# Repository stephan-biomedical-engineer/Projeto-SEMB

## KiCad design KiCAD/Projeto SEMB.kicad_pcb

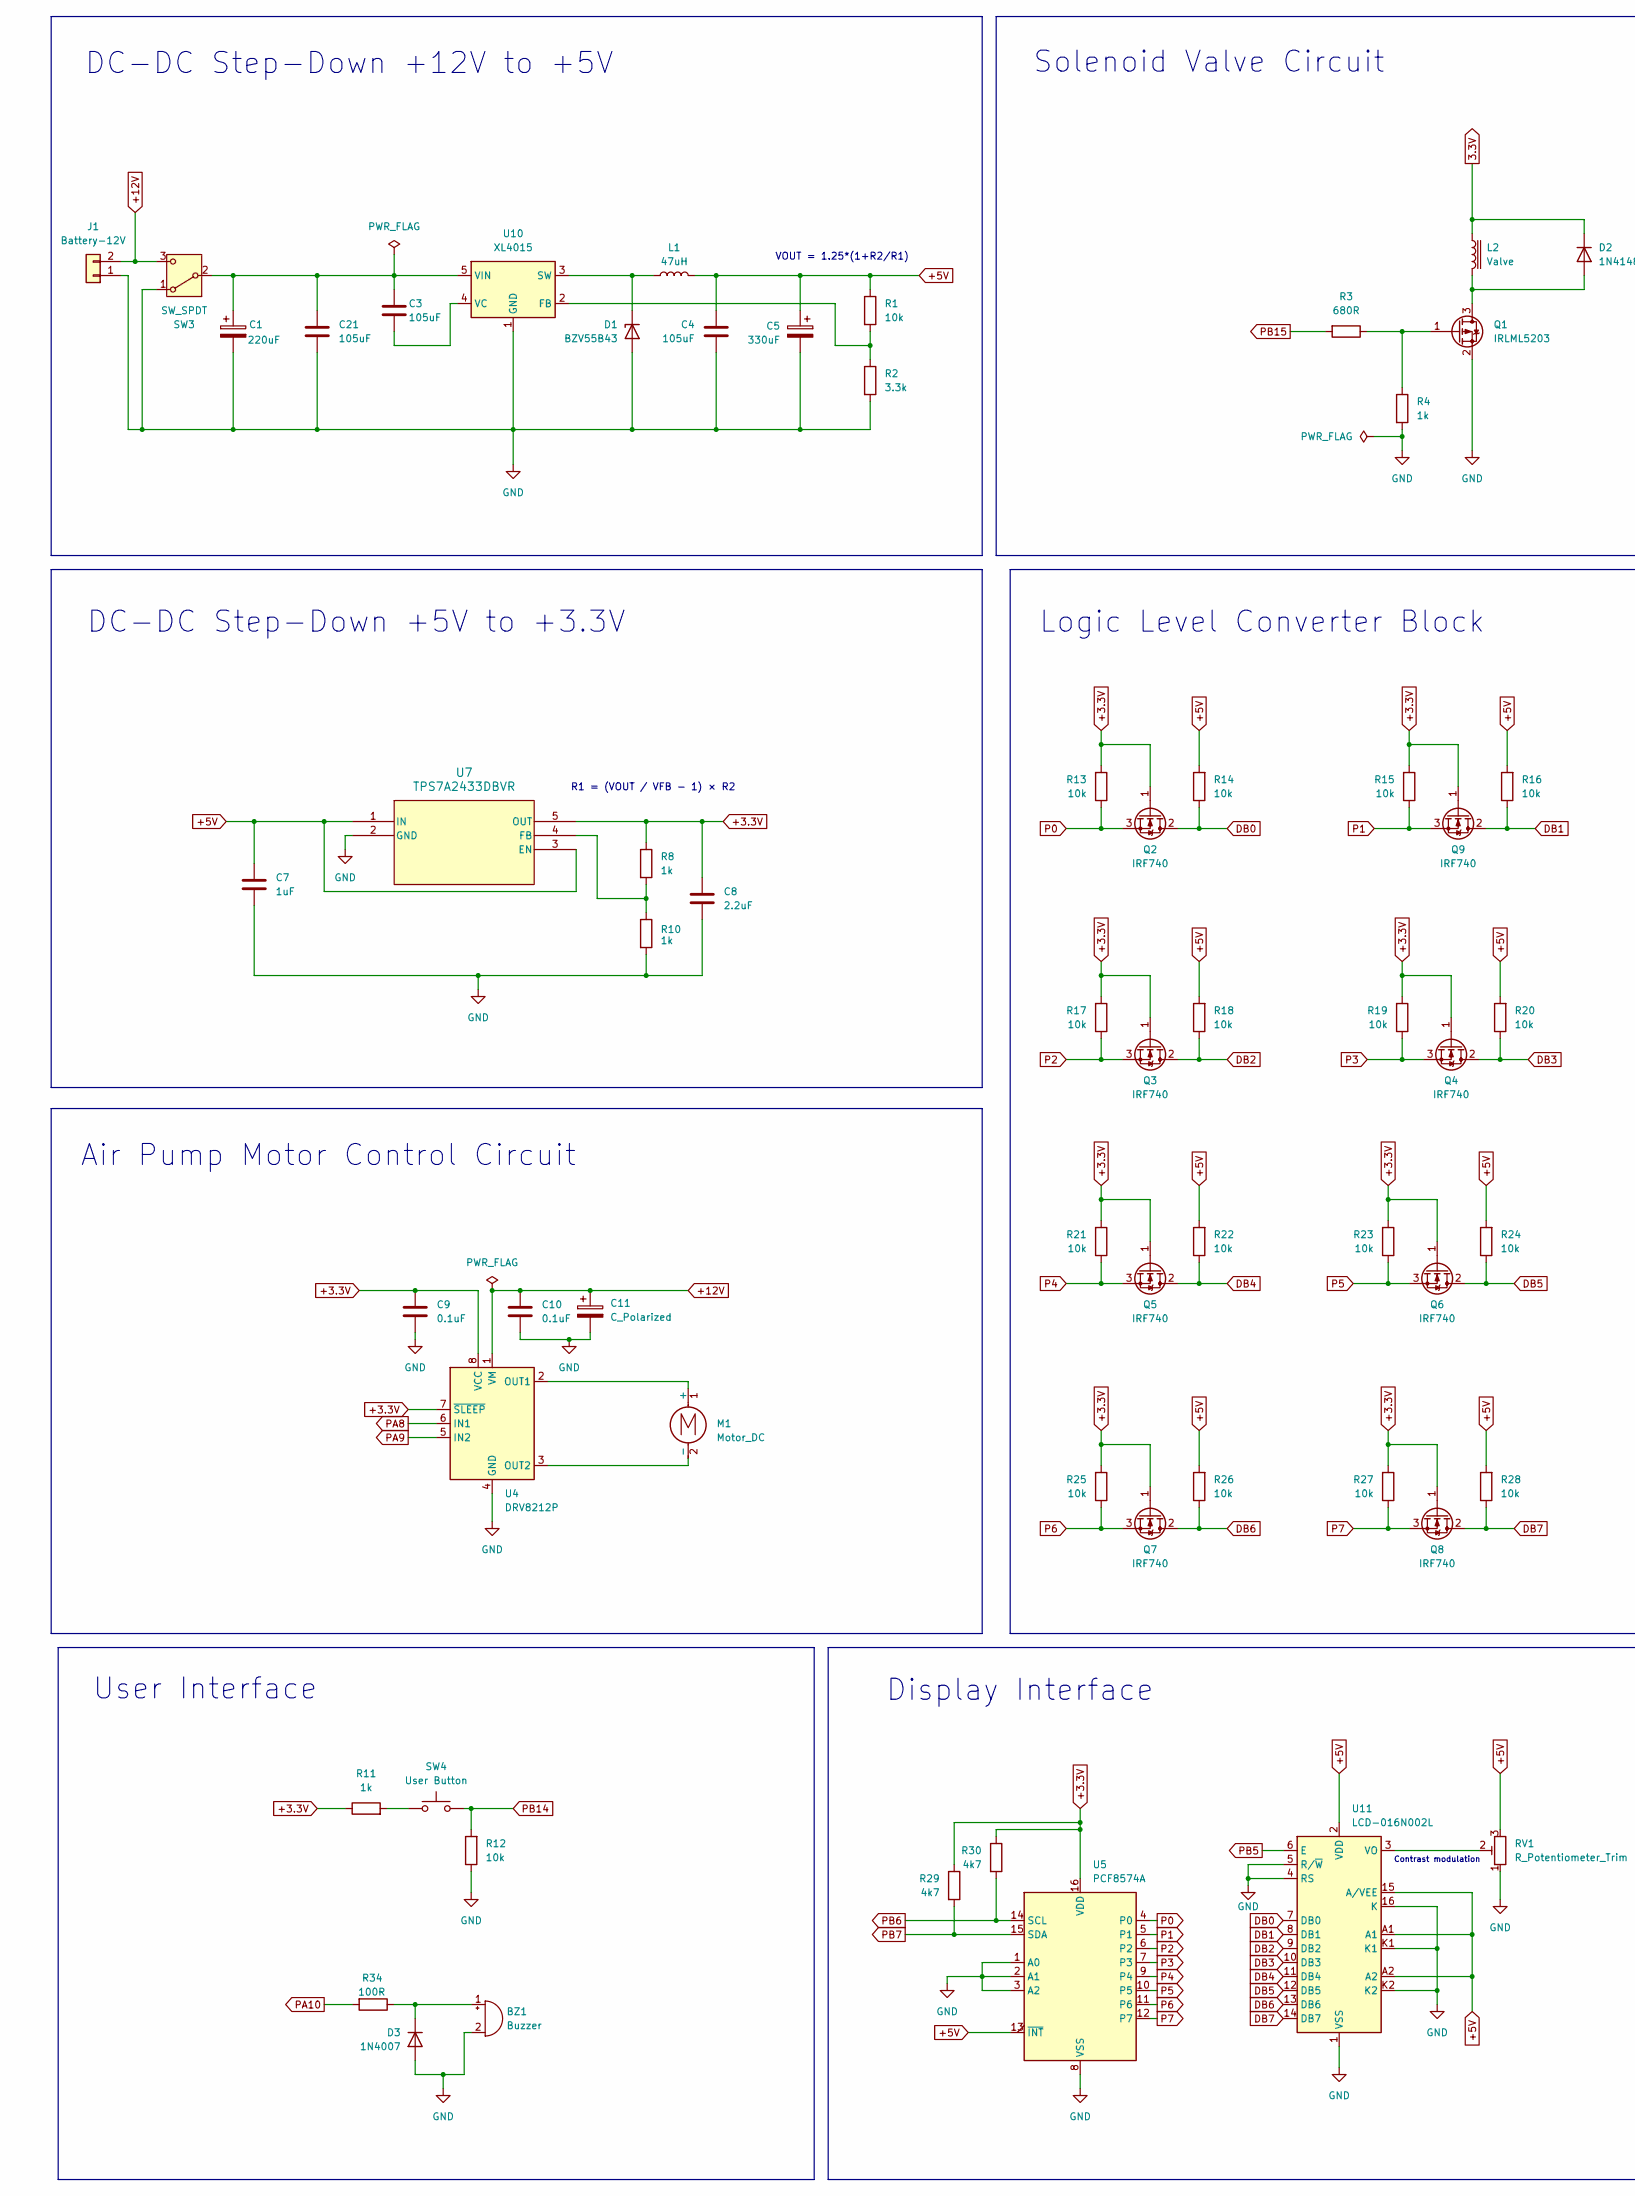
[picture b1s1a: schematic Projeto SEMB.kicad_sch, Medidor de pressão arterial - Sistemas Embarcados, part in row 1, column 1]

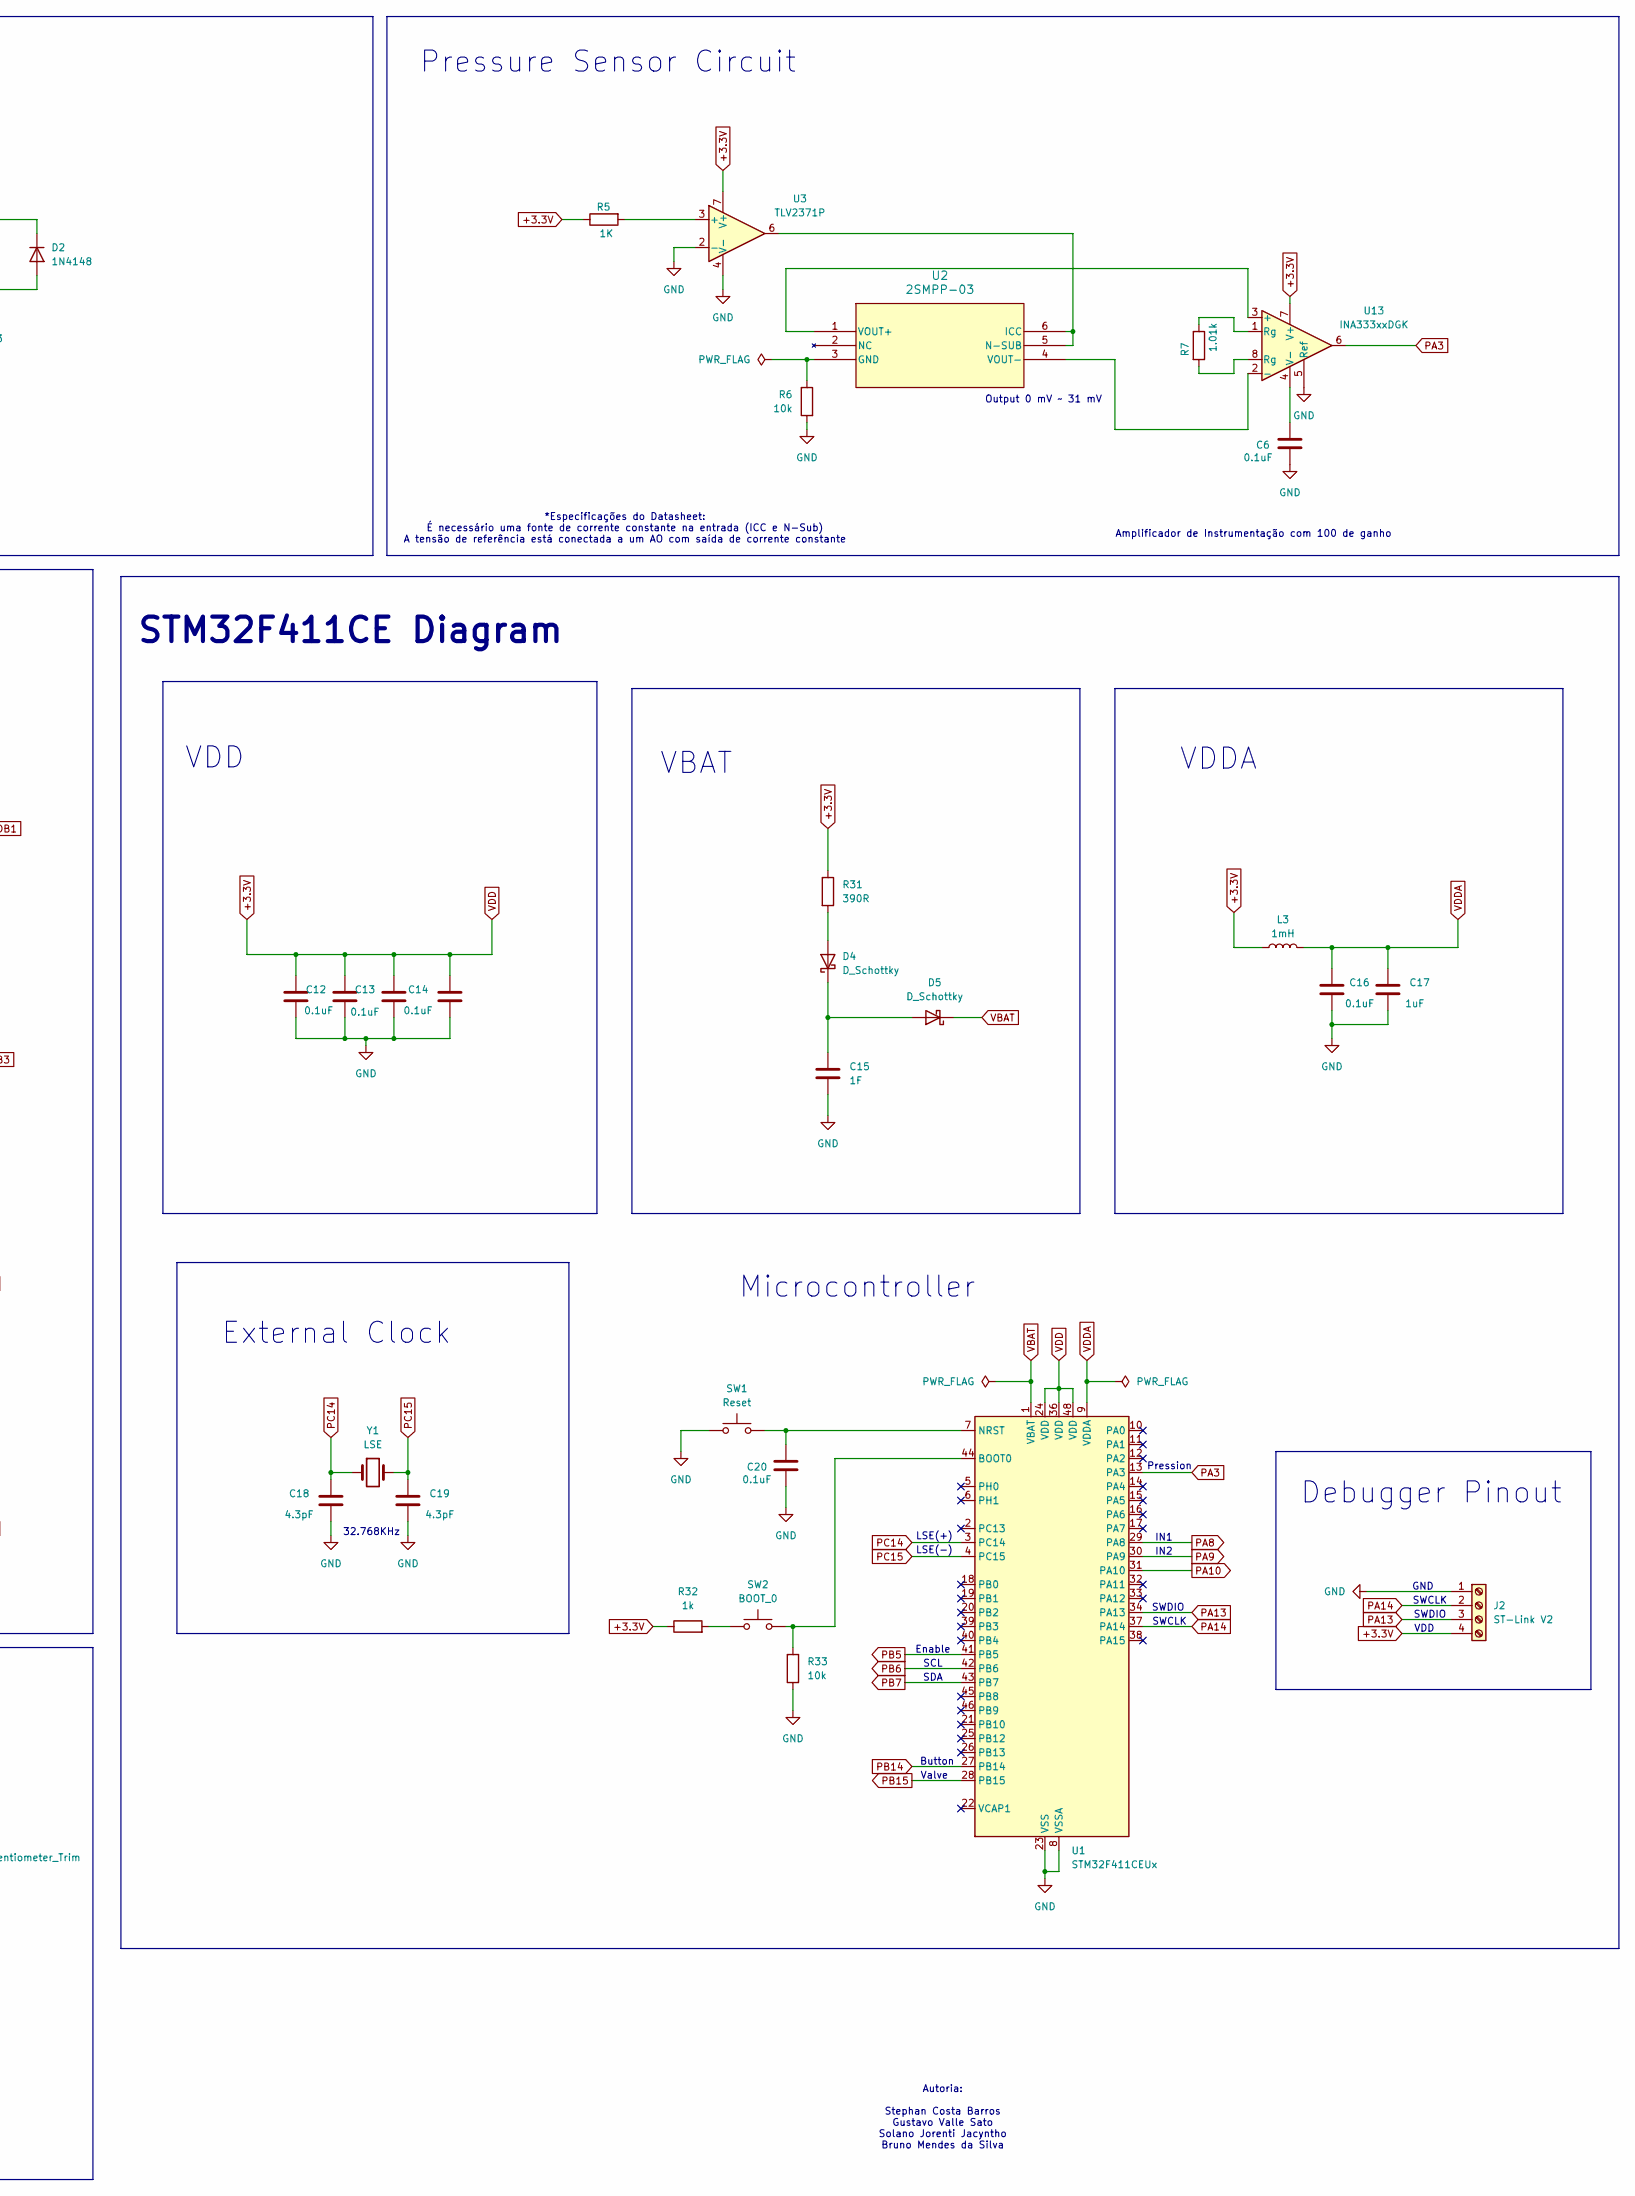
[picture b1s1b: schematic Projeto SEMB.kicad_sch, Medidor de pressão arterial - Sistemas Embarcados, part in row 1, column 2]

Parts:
BZ1: Buzzer; Buzzer_Mallory_AST1109MLTRQ
C1: 220uF; C_0603_1608Metric
C2: 4.7uF; C_0603_1608Metric
C3, C4, C21: 105uF; C_0603_1608Metric
C5: 330uF; C_0603_1608Metric
C6, C9, C10, C12, C13, C14, C16, C20: 0.1uF; C_0603_1608Metric
C7, C17: 1uF; C_0603_1608Metric
C8: 2.2uF; C_0603_1608Metric
C11: C_Polarized; C_0603_1608Metric
C15: 1F; CP_Radial_D8.0mm_P3.80mm
C18, C19: 4.3pF; C_0603_1608Metric
D1: BZV55B43; D_MiniMELF
D2: 1N4148; D_DO-35_SOD27_P7.62mm_Horizontal
D3: 1N4007; D_DO-41_SOD81_P10.16mm_Horizontal
D4, D5: D_Schottky; D_0201_0603Metric
J1: Battery-12V; PinHeader_1x02_P2.00mm_Vertical
J2: ST-Link V2; PinHeader_1x04_P2.00mm_Vertical
L1: 47uH; L_0603_1608Metric
L2: Valve; PinHeader_1x02_P2.00mm_Vertical
L3: 1mH; L_0603_1608Metric
M1: Motor_DC; PinHeader_1x02_P2.00mm_Vertical
Q1: IRLML5203; SOT-23
Q2, Q3, Q4, Q5, Q6, Q7, Q8, Q9: IRF740; TO-220-3_Vertical
R1, R6, R12, R13, R14, R15, R16, R17, R18, R19, R20, R21, R22, R23, R24, R25, R26, R27, R28, R33: 10k; R_0603_1608Metric_Pad0.98x0.95mm_HandSolder
R2: 3.3k; R_0603_1608Metric_Pad0.98x0.95mm_HandSolder
R3: 680R; R_0603_1608Metric_Pad0.98x0.95mm_HandSolder
R4, R8, R10, R11, R32: 1k; R_0603_1608Metric_Pad0.98x0.95mm_HandSolder
R5: 1K; R_0603_1608Metric_Pad0.98x0.95mm_HandSolder
R7: 1.01k; R_0603_1608Metric_Pad0.98x0.95mm_HandSolder
R29, R30: 4k7; R_0603_1608Metric_Pad0.98x0.95mm_HandSolder
R31: 390R; R_0603_1608Metric_Pad0.98x0.95mm_HandSolder
R34: 100R; R_0603_1608Metric_Pad0.98x0.95mm_HandSolder
RV1: R_Potentiometer_Trim; Potentiometer_Bourns_3269W_Vertical
SW1: Reset; SW_SPST_B3U-1000P-B
SW2: BOOT_0; SW_SPST_B3U-1000P-B
SW3: SW_SPDT; SW_SPST_PTS645
SW4: User Button; SW_SPST_B3U-1000P-B
U1: STM32F411CEUx; QFN-48-1EP_7x7mm_P0.5mm_EP5.6x5.6mm
U2: 2SMPP-03; 2SMPP-03_OMR
U3: TLV2371P; DIP-8_W7.62mm
U4: DRV8212P; WSON-8-1EP_2x2mm_P0.5mm_EP0.9x1.6mm_ThermalVias
U5: PCF8574A; SOIC127P1032X265-16N
U7: TPS7A2433DBVR; SOT23_DBV_TEX
U10: XL4015; TO-263-5_TabPin3
U11: LCD-016N002L
U13: INA333xxDGK; VSSOP-8_3x3mm_P0.65mm
Y1: LSE; Crystal_SMD_SeikoEpson_FA238V-4Pin_3.2x2.5mm

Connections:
3.3V: D2.1 (K), L2.1
+3.3V: C2.1, C8.1, C9.1, C12.1, C13.1, C14.1, J2.4, L3.1, Q2.1 (G), Q3.1 (G), Q4.1 (G), Q5.1 (G), Q6.1 (G), Q7.1 (G), Q8.1 (G), Q9.1 (G), R5.1, R8.1, R11.1, R13.2, R15.2, R17.2, R19.2, R21.2, R23.2, R25.2, R27.2, R29.1, R30.1, R31.1, R32.1, U1.24 (VDD), U1.36 (VDD), U1.48 (VDD), U3.7 (V+), U4.7 (~SLEEP), U4.8 (VCC), U5.16 (VDD), U7.5 (OUT), U13.7 (V+)
+5V: C4.1, C5.1, C7.1, L1.2, R1.1, R14.2, R16.2, R18.2, R20.2, R22.2, R24.2, R26.2, R28.2, RV1.3, U5.13 (~INT), U7.1 (IN), U7.3 (EN), U11.2 (VDD), U11.15 (A/VEE), U11.A1, U11.A2
+12V: C10.1, C11.1, J1.2, SW3.3 (C), U4.1 (VM)
DB0: Q2.2 (D), R14.1, U11.7 (DB0)
DB1: Q9.2 (D), R16.1, U11.8 (DB1)
DB2: Q3.2 (D), R18.1, U11.9 (DB2)
DB3: Q4.2 (D), R20.1, U11.10 (DB3)
DB4: Q5.2 (D), R22.1, U11.11 (DB4)
DB5: Q6.2 (D), R24.1, U11.12 (DB5)
DB6: Q7.2 (D), R26.1, U11.13 (DB6)
DB7: Q8.2 (D), R28.1, U11.14 (DB7)
GND: BZ1.2 (-), C1.2, C2.2, C4.2, C5.2, C6.2, C7.2, C8.2, C9.2, C10.2, C11.2, C12.2, C13.2, C14.2, C15.2, C16.2, C17.2, C18.2, C19.2, C20.2, C21.2, D1.2 (A), D3.2 (A), J1.1, J2.1, Q1.2 (S), R2.2, R4.2, R6.2, R10.2, R12.1, R33.1, RV1.1, SW1.1, SW3.1 (A), U1.8 (VSSA), U1.23 (VSS), U1.35 (VSS), U1.47 (VSS), U1.49 (VSS), U3.2 (-), U3.4 (V-), U4.4 (GND), U4.9 (GND), U5.1 (A0), U5.2 (A1), U5.3 (A2), U5.8 (VSS), U7.2 (GND), U10.1 (GND), U11.1 (VSS), U11.4 (RS), U11.5 (R/~W), U11.16 (K), U11.K1, U11.K2, U13.5 (Ref)
unnamed: BZ1.1 (+), D3.1 (K), R34.1
unnamed: D1.1 (K), L1.1, U10.3 (SW)
unnamed: D2.2 (A), L2.2, Q1.3 (D)
unnamed: D4.2 (A), R31.2
unnamed: C15.1, D4.1 (K), D5.2 (A)
unnamed: M1.1 (+), U4.2 (OUT1)
unnamed: M1.2 (-), U4.3 (OUT2)
unnamed: Q1.1 (G), R3.1, R4.1
unnamed: R7.1, U13.1 (Rg)
unnamed: R7.2, U13.8 (Rg)
unnamed: R11.2, SW4.1
unnamed: R32.2, SW2.1
unnamed: C1.1, C3.1, C21.1, SW3.2 (B), U10.5 (VIN)
unnamed: R33.2, SW2.2, U1.44 (BOOT0)
unnamed: C20.1, SW1.2, U1.7 (NRST)
unnamed: R6.1, U2.3 (GND)
unnamed: U2.5 (N-SUB), U2.6 (ICC), U3.6
unnamed: R5.2, U3.3 (+)
unnamed: R8.2, R10.1, U7.4 (FB)
unnamed: R1.2, R2.1, U10.2 (FB)
unnamed: C3.2, U10.4 (VC)
unnamed: RV1.2, U11.3 (VO)
unnamed: U2.1 (VOUT+), U13.3 (+)
unnamed: U2.4 (VOUT-), U13.2 (-)
unnamed: C6.1, U13.4 (V-)
P0: Q2.3 (S), R13.1, U5.4 (P0)
P1: Q9.3 (S), R15.1, U5.5 (P1)
P2: Q3.3 (S), R17.1, U5.6 (P2)
P3: Q4.3 (S), R19.1, U5.7 (P3)
P4: Q5.3 (S), R21.1, U5.9 (P4)
P5: Q6.3 (S), R23.1, U5.10 (P5)
P6: Q7.3 (S), R25.1, U5.11 (P6)
P7: Q8.3 (S), R27.1, U5.12 (P7)
PA3: U1.13 (PA3), U13.6
PA8: U1.29 (PA8), U4.6 (IN1)
PA9: U1.30 (PA9), U4.5 (IN2)
PA10: R34.2, U1.31 (PA10)
PA13: J2.3, U1.34 (PA13)
PA14: J2.2, U1.37 (PA14)
PB5: U1.41 (PB5), U11.6 (E)
PB6: R30.2, U1.42 (PB6), U5.14 (SCL)
PB7: R29.2, U1.43 (PB7), U5.15 (SDA)
PB14: R12.2, SW4.2, U1.27 (PB14)
PB15: R3.2, U1.28 (PB15)
PC14: C18.1, U1.3 (PC14), Y1.1
PC15: C19.1, U1.4 (PC15), Y1.2
VBAT: D5.1 (K), U1.1 (VBAT)
VDDA: C16.1, C17.1, L3.2, U1.9 (VDDA)

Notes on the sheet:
User Interface
GND
VDD
Solenoid Valve Circuit
Logic Level Converter Block
Microcontroller
DC-DC Step-Down +5V to +3.3V
R1 = (VOUT / VFB - 1) × R2
External Clock
STM32F411CE Diagram
SWCLK
Pression
DC-DC Step-Down +12V to +5V
IN1
Output 0 mV ~ 31 mV
IN2
Autoria: Stephan Costa Barros Gustavo Valle Sato Solano Jorenti Jacyntho Bruno Mendes da Silva
Amplificador de Instrumentação com 100 de ganho
VBAT
Display Interface
Air Pump Motor Control Circuit
VOUT = 1.25*(1+R2/R1)
Valve
Contrast modulation
Button
SWDIO
32.768KHz
Debugger Pinout
SCL
SDA
VDDA
SWCLK
Enable
*Especificações do Datasheet: É necessário uma fonte de corrente constante na entrada (ICC e N-Sub) A tensão de referência está conectada a um AO com saída de corrente constante
LSE(-)
LSE(+)
Pressure Sensor Circuit

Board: 2 copper layers, 90 parts (0 on the bottom side), 61 nets, no tracks yet.

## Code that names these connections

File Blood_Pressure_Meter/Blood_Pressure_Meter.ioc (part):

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Mcu.Name=STM32F411C(C-E)Ux
Mcu.Package=UFQFPN48
Mcu.UserName=STM32F411CEUx
PA10.GPIOParameters=PinState,GPIO_PuPd,GPIO_Label
PA10.GPIO_Label=Buzzer
PA10.GPIO_PuPd=GPIO_PULLDOWN
PA10.PinState=GPIO_PIN_RESET
PA10.Signal=GPIO_Output
PA13.Mode=Serial_Wire
PA13.Signal=SYS_JTMS-SWDIO
PA14.Mode=Serial_Wire
PA14.Signal=SYS_JTCK-SWCLK
PA3.Signal=ADCx_IN3
PA8.GPIOParameters=GPIO_PuPd,GPIO_Label
PA8.GPIO_Label=IN1_Motor_OUT
PA8.GPIO_PuPd=GPIO_NOPULL
PA8.Signal=GPIO_Output
PA9.GPIOParameters=GPIO_PuPd,GPIO_Label,GPIO_ModeDefaultOutputPP
PA9.GPIO_Label=IN2_Motor_OUT
PA9.GPIO_ModeDefaultOutputPP=GPIO_MODE_OUTPUT_PP
PA9.GPIO_PuPd=GPIO_NOPULL
PA9.Signal=GPIO_Output
PB14.GPIOParameters=GPIO_PuPd,GPIO_Label
PB14.GPIO_Label=Button
PB14.GPIO_PuPd=GPIO_PULLDOWN
PB14.Signal=GPIO_Input
PB15.GPIOParameters=GPIO_PuPd,GPIO_Label
PB15.GPIO_Label=Valve_OUT
PB15.GPIO_PuPd=GPIO_PULLDOWN
PB15.Signal=GPIO_Output
PB5.GPIOParameters=PinState,GPIO_PuPd,GPIO_Label
PB5.GPIO_Label=LCD_Enable_OUT
PB5.GPIO_PuPd=GPIO_PULLDOWN
PB5.PinState=GPIO_PIN_SET
PB5.Signal=GPIO_Output
PB6.Mode=I2C
PB6.Signal=I2C1_SCL
PB7.Mode=I2C
PB7.Signal=I2C1_SDA
PC14-OSC32_IN.Mode=LSE-External-Oscillator
PC14-OSC32_IN.Signal=RCC_OSC32_IN
PC15-OSC32_OUT.Mode=LSE-External-Oscillator
PC15-OSC32_OUT.Signal=RCC_OSC32_OUT
RCC.HSE_VALUE=25000000
RCC.SYSCLKFreq_VALUE=64000000
RCC.SYSCLKSource=RCC_SYSCLKSOURCE_PLLCLK
board=custom

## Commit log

2024-09-20 Correção Sensor de Pressão KiCAD
2024-09-20 Deletando o código do CubeIDE
2024-09-22 Mudanças no Esquemático -> Priorização do Circuito com Driver do Motor DC e Correção dos Warnings do Electrical Rule Checker
2024-09-22 Atualização de Datasheets e inclusão do LCD com expansor I²C
2024-09-26 PRJ2-Final
2024-10-25 Footprints
2024-10-26 Implementação do Código
2024-10-26 User Interface
2024-10-28 Atualizando esquemático
2024-10-31 substitute
2024-10-31 susbtitute
2024-11-05 código atualizado
